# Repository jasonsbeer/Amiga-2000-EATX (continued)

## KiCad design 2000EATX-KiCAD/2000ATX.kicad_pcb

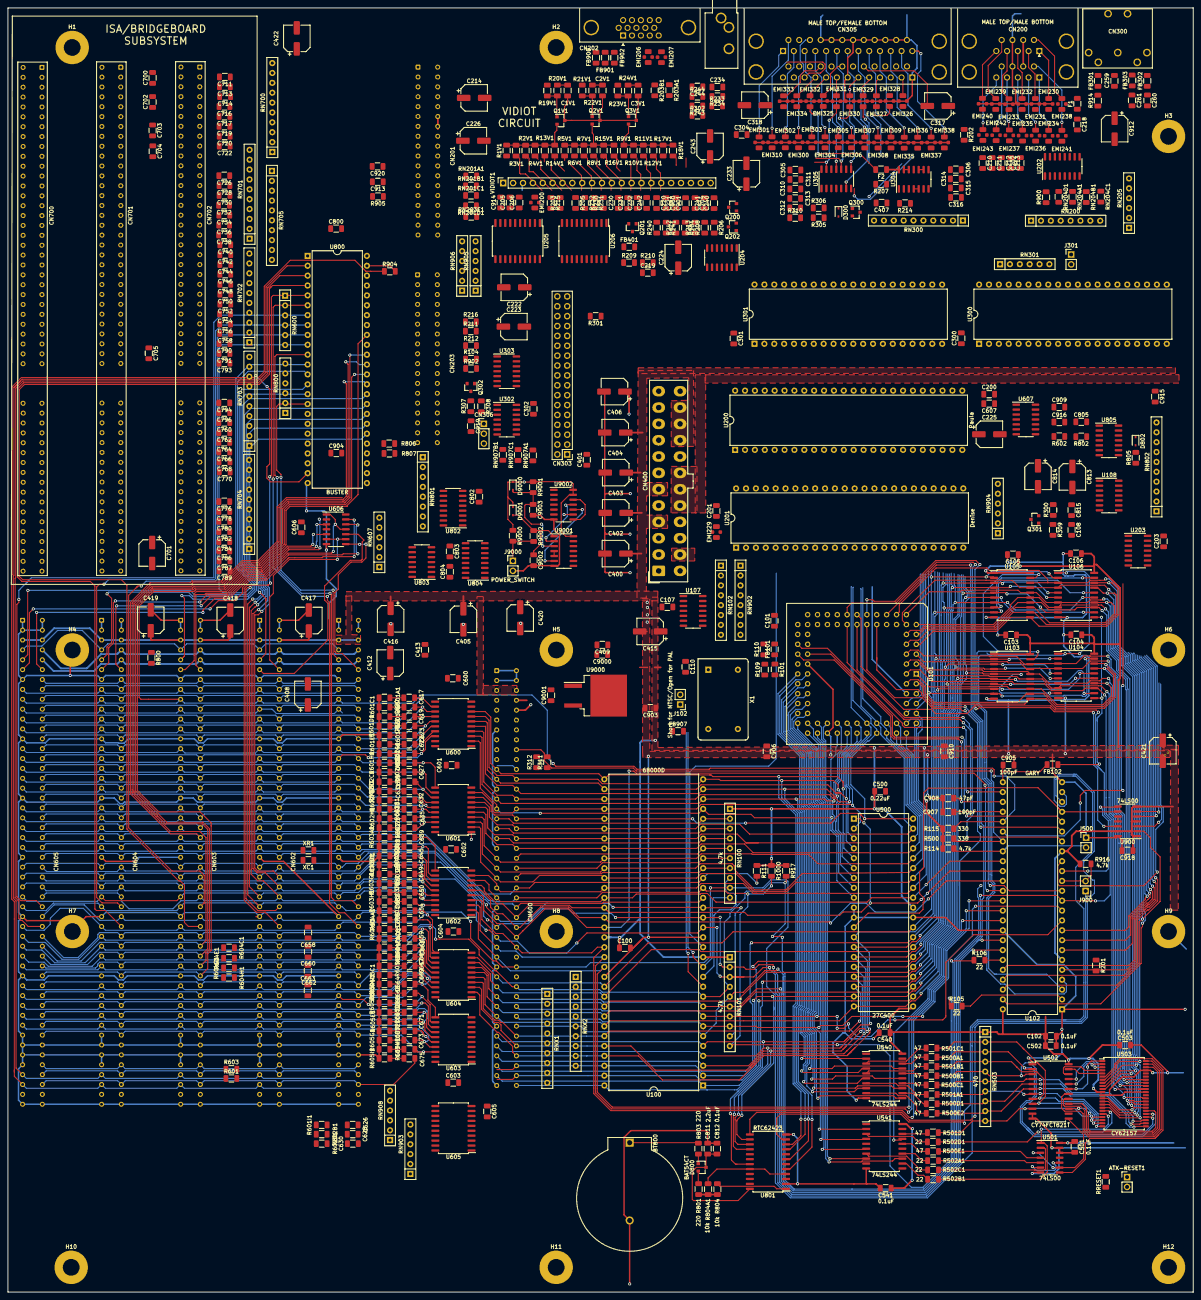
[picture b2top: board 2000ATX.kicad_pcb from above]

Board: 2 copper layers, 304.8 x 330.2 mm, 579 parts (0 on the bottom side), 722 nets.

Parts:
ATX-RESET1: ATX RESET; PinHeader_1x02_P2.54mm_Vertical
BT800: Battery_Cell; BatteryHolder_ComfortableElectronic_CH273-2450_1x2450
C1V1, C2V1, C3V1: 100nF; C_1206_3216Metric
C100, C101, C102, C103, C104, C105, C106, C107, C108, C110, C200, C202, C203, C204, C205, C206, C218, C230, C234, C240, C244, C300, C301, C302, C305, C501, C502, C503, C540, C541, C600, C601, C602, C603, C604, C605, C606, C607, C800, C802, C803, C804, C805, C812, C815, C900, C901, C909, C915, C916, C918, C919: 0.1uF; C_1206_3216Metric
C201, C219, C220, C221, C500, C700, C702, C703, C704, C705: 0.22uF; C_1206_3216Metric
C210, C211, C212, C213: 0.047uF; C_1206_3216Metric
C214, C225, C226, C912: 470uF; CP_Elec_6.3x5.8
C222, C223, C402, C403, C404, C405, C406, C408, C412, C420, C421, C422: 47uF; CP_Elec_6.3x5.8
C224, C415: 4.7uF; CP_Elec_6.3x5.8
C231, C241: 6800pF; C_1206_3216Metric
C232, C242: 3900pF; C_1206_3216Metric
C233, C243, C317, C318, C701, C813, C814: 22uF; CP_Elec_6.3x5.8
C259, C260, C261, C304, C306, C904, C905, C907, C914, C920: 100pF; C_1206_3216Metric
C310, C311, C312, C313, C314, C315, C316, C617, C619, C620, C621, C622, C623, C624, C625, C626, C627, C628, C629, C630, C631, C632, C633, C635, C637, C639, C641, C645, C647, C649, C650, C651, C652, C654, C655, C657, C658, C659, C660, C661, C662, C663, C664, C665, C666, C667, C668, C669, C670, C671, C672, C673, C674, C675, C711, C713, C714, C716, C717, C719, C720, C722, C726, C728, C730, C732, C734, C736, C738, C740, C742, C744, C746, C748, C750, C752, C754, C756, C758, C760, C762, C764, C766, C768, C770, C776, C778, C780, C782, C784, C786, C787, C789, C790, C791, C793, C794, C796: 1000pF; C_1206_3216Metric
C400, C416, C417, C418, C419: 220uF; CP_Elec_6.3x5.8
C401, C407, C409, C413, C903, C906, C910: 0.1uf; C_1206_3216Metric
C811: 2.2uF; C_1206_3216Metric
C908, C913: 47pF; C_1206_3216Metric
C9000, C9002: 1uF; C_1206_3216Metric
C9001: 0.33uF; C_1206_3216Metric
C9003: 10uF; C_1206_3216Metric
CN200: DB9_Male_Stack; DSUB-9_Male_Stack
CN201, CN203: Amiga-2000-Video-Slot; 2x18_P2.54mm_Horizontal
CN202: DB15_Female_HighDensity; DSUB-15-HD_Female_Horizontal_P2.29x1.98mm_EdgePinOffset3.03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
CN205: AudioJack; Jack_3.5mm_CUI_SJ1-3533NG_Horizontal_CircularHoles
CN300: KEYBOARD; DIN5
CN303: FLOPPY; PinHeader_2x17_P2.54mm_Vertical
CN305: DB25_Stack_FemaleAndMale; DSUB-25_Stack_Female_Bottom_Male_Top
CN306: POWER LED; PinHeader_1x03_P2.54mm_Vertical
CN400: ATX-24; Molex_Mini-Fit_Jr_5566-24A_2x12_P4.20mm_Vertical
CN600: Amiga-2000-CPU-Slot; Samtec_HLE-150-02-xx-DV-TE_2x43_P2.54mm_Horizontal
CN601, CN602, CN603, CN604, CN605: Amiga-2000-Zorro-Slot; Samtec_HLE-150-02-xx-DV-TE_2x50_P2.54mm_Horizontal
CN700, CN701, CN702: ISA-16-BIT-Slot; ISA_16-BIT_P2.54mm_Horizontal
D300, D802, D9000, D9001: 1N4148; D_SOD-323
D800: BAT54CT; SOT-23
EMI200, EMI206, EMI207, EMI229, EMI230, EMI231, EMI232, EMI233, EMI234, EMI235, EMI236, EMI237, EMI238, EMI239, EMI240, EMI241, EMI242, EMI243, EMI325, EMI326, EMI327, EMI328, EMI329, EMI330, EMI331, EMI332, EMI333, EMI334: 100pF; C_1206_3216_Feedthrough
EMI300, EMI301, EMI302, EMI303, EMI304, EMI305, EMI306, EMI307, EMI308, EMI309, EMI310, EMI335, EMI336, EMI337, EMI338: C_Feedthrough; C_1206_3216_Feedthrough
F1, F2: 4A; Fuse_1206_3216Metric
FB101, FB102, FB301, FB302, FB303, FB401, FB900, FB901, FB902, FB907: Ferrite_Bead; C_1206_3216Metric
H1, H2, H3, H4, H5, H6, H7, H8, H9, H10, H11, H12: MountingHole_Pad; MountingHole_4.3mm_M4_Pad
J102: Short for NTSC/Open for PAL; PinHeader_1x02_P2.54mm_Vertical
J301: CLOSE FOR DF1; PinHeader_1x02_P2.54mm_Vertical
J500: Conn_01x02_Male; PinHeader_1x02_P2.54mm_Vertical
J900: Enable Chip RAM slowdown during DMA; PinHeader_1x02_P2.54mm_Vertical
J9000: POWER_SWITCH; PinHeader_1x02_P2.54mm_Vertical
Q1V1, Q2V1, Q3V1, Q300: MMBT3904; SOT-23
Q200, Q201: MMBFJ211; SOT-23
Q202, Q301, Q302: MMBT3906; SOT-23
R1V1, R5V1, R9V1, R233, R243, R301, R302, R311, R312, R601, R601A1, R601B1, R601C1, R601D1, R601E1, R601F1, R601G1, R601H1, R601I1, R602, R602A1, R602B1, R602C1, R602D1, R602E1, R602F1, R602G1, R602H1, R602I1, R603, R603A1, R603B1, R603C1, R603D1, R603E1, R603F1, R603G1, R603H1, R603I1, R604, R604A1, R604B1, R604C1, R604D1, R604E1, R604F1, R604G1, R604H1, R604I1, R605, R605A1, R605B1, R605C1, R605D1, R605E1, R605F1, R605G1, R605H1, R605I1, R800, R802, R805, R900: 1k; R_1206_3216Metric
R2V1, R7V1, R11V1: 4k; R_1206_3216Metric
R3V1, R6V1, R10V1: 2k; R_1206_3216Metric
R4V1, R8V1, R12V1: 8k; R_1206_3216Metric
R13V1, R15V1, R17V1, R9002: 470; R_1206_3216Metric
R14V1, R16V1, R18V1, R234, R244: 390; R_1206_3216Metric
R19V1, R20V1, R21V1, R22V1, R23V1, R24V1: 75; R_1206_3216Metric
R101, R109, R201, R300, R309, R500, R806, R807, R902, R916: 4.7k; R_1206_3216Metric
R104: 4.7k; C_1206_3216Metric
R105, R106, R212, R502A1, R502B1, R502C1, R502D1: 22; R_1206_3216Metric
R110, R114, R115: 330; R_1206_3216Metric
R111, R917, R1000: 407; C_1206_3216Metric
R202, R203, R206, R211, R214, R216, R231, R232, R241, R242, R305, R306, R804, R804A1, R9000, R9001: 10k; R_1206_3216Metric
R203A1, R203B1, R500A1, R500B1, R500C1, R500D1, R500E1, R500E2, R501A1, R501B1, R501C1, R501D1, R904, R905: 47; R_1206_3216Metric
R204, R205: 470k; R_1206_3216Metric
R207, R208: 10; R_1206_3216Metric
R209, R210: 1.2k; R_1206_3216Metric
R213: 2.7k; R_1206_3216Metric
R215: 1; R_1206_3216Metric
R230, R240: 360; R_1206_3216Metric
R307: 68; R_1206_3216Metric
R308: 200; R_1206_3216Metric
R310: 47 0.5W; R_1206_3216Metric
R801, R803: 220; R_1206_3216Metric
R914: 1 0.5W; R_1206_3216Metric
RN100, RN101: 4.7k; R_Array_SIP10
RN102, RN902: 47; R_Array_SIP8
RN200, RN801: 4.7k; R_Array_SIP8
RN201A1, RN201B1, RN201C1, RN201D1, RN203E1, RN907A1, RN907B1, RN907C1: 47; R_1206_3216Metric
RN204A1, RN204B1, RN204C1, RN204D1: 68; R_1206_3216Metric
RN205, RN301, RN607, RN800, RN903, RN908: 1k; R_Array_SIP6
RN300: 10k; R_Array_SIP10
RN503: 470; R_Array_SIP10
RN600: 10k; R_Array_SIP6
RN700, RN701, RN702, RN703, RN704, RN705, RN802: 1k; R_Array_SIP10
RN904, RN905, RN906: 4.7k; R_Array_SIP6
RNX1, RNX2: 2.7k; R_Array_SIP10
RRESET1: 1k; R_1206_3216Metric
U100: 68000D; DIP-64_W25.4mm
U101: FATTERAGNUS; PLCC-84_THT-Socket
U102: GARY; DIP-48_W15.24mm
U103, U105, U600, U601, U602, U603, U604, U605: 74LS245; SOIC-20W_7.5x12.8mm_P1.27mm
U104, U106: 74LS373; SOIC-20W_7.5x12.8mm_P1.27mm
U107: 74LS04; SOIC-14_3.9x8.7mm_P1.27mm
U108: 74LS74; SOIC-14_3.9x8.7mm_P1.27mm
U200: Paula; DIP-48_W15.24mm
U201: Denise; DIP-48_W15.24mm
U202: 74LS157; SOIC-16_3.9x9.9mm_P1.27mm
U203: 74LS38; SOIC-14_3.9x8.7mm_P1.27mm
U204: LF347; SOIC-14_3.9x8.7mm_P1.27mm
U205, U206: 74HCT244; SOIC-20W_7.5x12.8mm_P1.27mm
U300: 8520; DIP-40_W15.24mm
U301: U8520; DIP-40_W15.24mm
U302, U606: 74LS32; SOIC-14_3.9x8.7mm_P1.27mm
U303, U607, U803: 74LS08; SOIC-14_3.9x8.7mm_P1.27mm
U304: SN75188DR; SOIC-14_3.9x8.7mm_P1.27mm
U305: SN75189DR; SOIC-14_3.9x8.7mm_P1.27mm
U500: 27C400; DIP-40_W15.24mm
U501, U900: 74LS00; SOIC-14_3.9x8.7mm_P1.27mm
U502: CY74FCT821T; SOIC-24W_7.5x15.4mm_P1.27mm
U503: CY62157; TSOP-II-44_10.16x18.41mm_P0.8mm
U540, U541: 74LS244; SOIC-20W_7.5x12.8mm_P1.27mm
U800: BUSTER; DIP-48_W15.24mm
U801: RTC62423; SOIC-24W_7.5x15.4mm_P1.27mm
U802: 74LS138; SOIC-16_3.9x9.9mm_P1.27mm
U804: 74LS148; SOIC-16_3.9x9.9mm_P1.27mm
U805: LM339; SOIC-14_3.9x8.7mm_P1.27mm
U9000: MC7905; TO-263-2
U9001: 74HC14; SOIC-14_3.9x8.7mm_P1.27mm
U9002: 74HC74; SOIC-14_3.9x8.7mm_P1.27mm
VIDIOT1: HY200; PinSocket_1x22_P2.54mm_Vertical
X1: 28.63636MHz; Oscillator_DIP-14
XC1: 270pf; C_1206_3216Metric
XR1: 68; C_1206_3216Metric

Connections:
7M: RN907A1.1, U100.15, U201.35
28M: CN600.9, FB101.2, U101.34
+3V3: CN400.1, CN400.2, CN400.12, CN400.13
+5V: C100.1, C101.1, C102.1, C103.1, C104.1, C105.1, C106.1, C107.1, C108.2, C110.1, C200.1, C202.2, C203.2, C218.1, C225.1, C300.2, C301.1, C302.2, C305.1, C400.1, C401.1, C402.1, C403.1, C404.1, C405.1, C415.1, C416.1, C417.1, C418.1, C419.1, C420.1, C421.1, C422.1, C500.1, C501.1, C502.1, C503.1, C540.1, C541.1, C605.2, C606.1, C607.2, C700.1, C701.1, C705.1, C800.1, C802.1, C803.1, C804.1, C805.1, C903.1, C906.1, C910.1, C918.1, CN201.6, CN201.8, CN400.4, CN400.6, CN400.21, CN400.22, CN400.23, CN600.5, CN600.6, CN601.5, CN601.6, CN602.5, CN602.6, CN603.5, CN603.6, CN604.5, CN604.6, CN605.5, CN605.6, CN700.B3, CN700.B29, CN700.D16, CN701.B3, CN701.B29, CN701.D16, CN702.B3, CN702.B29, CN702.D16, D802.1, EMI200.1, EMI229.1, F1.1, Q302.1, R101.2, R104.1, R109.2, R111.1, R114.2, R115.2, R201.1, R203.2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
+12V: C406.1, C407.1, C704.1, CN201.10, CN400.10, CN400.11, CN600.10, CN601.10, CN602.10, CN603.10, CN604.10, CN605.10, CN700.B9, CN701.B9, CN702.B9, F2.1, R207.1, U304.14
+AV: C220.1, C222.1, C900.1, Q202.1, R207.2, R213.1, U204.4
+VID: C205.2, C206.2, C214.1, C226.1, R215.1, U205.20, U206.20, VIDIOT1.2, VIDIOT1.21
-5V: C412.1, C413.1, C702.1, C9001.1, CN201.31, CN600.8, CN601.8, CN602.8, CN603.8, CN604.8, CN605.8, CN700.B5, CN701.B5, CN702.B5, U9000.3
-12V: C408.1, C409.1, C703.1, C9000.1, CN400.14, CN601.20, CN602.20, CN603.20, CN604.20, CN605.20, CN700.B7, CN701.B7, CN702.B7, EMI334.2, R208.2, U304.1, U9000.2
-AV: C221.2, C223.2, C901.2, R206.2, R208.1, U204.11
/Floppy and Parallel/CHNG: CN303.2, RN301.2, U300.4
/Floppy and Parallel/DKWDB: CN303.22, U203.8
/Floppy and Parallel/DKWEB: CN303.24, U203.11
/Floppy and Parallel/INUSE1: CN303.4, CN303.14, U108.9, U203.4
/Floppy and Parallel/KBCLK: C260.1, CN300.3, FB302.1
/Floppy and Parallel/KBDATA: C261.1, CN300.2, FB303.1
/Floppy and Parallel/MTROD: CN303.16, Q301.3
/Floppy and Parallel/POUT: CN305.12, EMI337.2
/Floppy and Parallel/RDY: CN303.34, J301.2, RN301.5, U300.7
/Floppy and Parallel/SEL: CN305.13, EMI338.2
/Floppy and Parallel/TRK0: CN303.26, RN301.3, U300.6
/Floppy and Parallel/WPROT: CN303.28, RN301.4, U300.5
/Floppy and Parallel/_INUSE0: CN303.6, U900.3
/Floppy and Parallel/_IORST: C916.1, EMI300.2, U607.8
/Memory and Kickstart/DRAB0: R500A1.1, RN503.3, U502.2, U503.27
/Memory and Kickstart/DRAB1: R500B1.1, RN503.5, U502.3, U503.26
/Memory and Kickstart/DRAB2: R500C1.1, RN503.6, U502.4, U503.25
/Memory and Kickstart/DRAB3: R500D1.1, RN503.8, U502.5, U503.24
/Memory and Kickstart/DRAB4: R500E2.1, RN503.9, U502.6, U503.23
/Memory and Kickstart/DRAB5: R501A1.1, RN503.7, U502.7, U503.22
/Memory and Kickstart/DRAB6: R501B1.1, RN503.4, U502.8, U503.21
/Memory and Kickstart/DRAB7: R501C1.1, RN503.2, U502.9, U503.20
/Memory and Kickstart/DRAB8: R501D1.1, RN503.10, U502.10, U503.19
/Memory and Kickstart/DRAC0: U502.23, U503.5
/Memory and Kickstart/DRAC1: U502.22, U503.4
/Memory and Kickstart/DRAC2: U502.21, U503.3
/Memory and Kickstart/DRAC3: U502.20, U503.2
/Memory and Kickstart/DRAC4: U502.19, U503.1
/Memory and Kickstart/DRAC5: U502.18, U503.44
/Memory and Kickstart/DRAC6: U502.17, U503.43
/Memory and Kickstart/DRAC7: U502.16, U503.42
/Memory and Kickstart/DRAC8: U502.15, U503.28
/Memory and Kickstart/_CAS: U501.6, U501.10
/Memory and Kickstart/_MCASL: R500E1.1, U501.4
/Memory and Kickstart/_MCASU: R502A1.1, U501.5
/Memory and Kickstart/_MEMCLK: U501.3, U501.9, U502.13
/Memory and Kickstart/_MRAS0: R502B1.1, U501.1, U503.18
/Memory and Kickstart/_MRAS1: R502C1.1, U501.2
/Memory and Kickstart/_MWE: R502D1.1, U503.17
/Memory and Kickstart/_SRAMCE: U501.8, U503.6
/Paula/+5VMOUSE: CN200.7, CN200.16, F1.2
/Paula/FIR0: CN200.15, EMI241.1
/Power/+5VSB: CN400.9, D9000.1, D9001.1, R9000.1, R9001.1, U9001.14, U9002.13, U9002.14
/Power/PS_ON: CN400.16, U9002.9
/Serial/+V: CN305.34, EMI332.1
/Serial/-V: CN305.35, EMI334.1
/Serial/AI: C306.1, C317.2, CN305.43
/Serial/AO: C304.1, C318.1, CN305.36
/Serial/CD: CN305.33, EMI331.2, U301.7, U305.11
/Serial/CTS: CN305.30, EMI329.2, U301.6, U305.6
/Serial/DSR: CN305.31, EMI330.2, U301.5, U305.8
/Serial/DTR: CN305.45, EMI325.2, U301.9, U304.12, U304.13
/Serial/RI: CN305.47, EMI333.1
/Serial/RTS: CN305.29, EMI327.2, U301.8, U304.4, U304.5
/Serial/RxD: CN305.28, EMI328.2
/Serial/TxD: CN305.27, EMI326.2
/Video/BLUE: C3V1.2, CN201.15, FB902.2, R18V1.1, R24V1.2, VIDIOT1.17
/Video/BURST: CN201.18, U205.16
/Video/COMPSYNC: CN201.28, VIDIOT1.20
/Video/DB_(B3): CN201.25, RN201B1.2
/Video/DG_(G3): CN201.27, RN201C1.2
/Video/DI_(B0): CN201.23, RN201A1.2
/Video/DR_(R3): CN201.29, RN201D1.2
/Video/GREEN: C2V1.2, CN201.11, FB901.2, R16V1.1, R22V1.2, VIDIOT1.12
/Video/HSYNC: EMI206.1, R203B1.1
/Video/PIXELSW: CN201.30, RN203E1.1
/Video/RED: C1V1.2, CN201.7, FB900.2, R14V1.1, R20V1.2, VIDIOT1.7
/Video/VSYNC: EMI207.1, R203A1.1
/Zorro_Expansion/_CFGIN1: CN605.11, RN607.5, U606.13
/Zorro_Expansion/_CFGIN2: CN604.11, RN607.4, U606.2
/Zorro_Expansion/_CFGIN3: CN603.11, RN607.3, U606.5
/Zorro_Expansion/_CFGIN4: CN602.11, RN607.2, U606.10
/Zorro_Expansion/_CFGOUT2: CN604.12, U606.1, U606.11
/Zorro_Expansion/_CFGOUT3: CN603.12, U606.3, U606.4
/Zorro_Expansion/_CFGOUT4: CN602.12, U606.6, U606.9
/Zorro_Expansion/_CFGOUT5: CN601.12, U606.8
A1: CN600.29, U100.29, U101.60, U500.9, U600.2
A2: CN600.27, U100.30, U101.61, U500.8, U600.3, U801.5
A3: CN600.26, U100.31, U101.62, U500.7, U600.5, U801.7
A4: CN600.24, U100.32, U101.63, U500.6, U600.7, U801.9
A5: CN600.21, U100.33, U101.64, U500.5, U600.8, U801.10
A6: CN600.23, U100.34, U101.65, U500.4, U600.6
A7: CN600.28, U100.35, U101.66, U500.3, U600.4
A8: CN600.30, U100.36, U101.67, U300.38, U301.38, U500.2, U601.9
A9: CN600.32, U100.37, U101.68, U300.37, U301.37, U500.40, U601.8
A10: CN600.34, U100.38, U101.69, U300.36, U301.36, U500.39, U601.7
A11: CN600.36, U100.39, U101.70, U300.35, U301.35, U500.38, U601.6
A12: CN600.38, U100.40, U101.71, U302.1, U500.37, U601.5
A13: CN600.39, U100.41, U101.72, U302.5, U500.36, U601.4
A14: CN600.41, U100.42, U101.73, U500.35, U601.3
A15: CN600.43, U100.43, U101.74, U500.34, U601.2
A16: CN600.45, U100.44, U101.75, U500.33, U602.9
A17: CN600.47, U100.45, U101.76, U102.33, U500.32, U602.8
A18: CN600.52, U100.46, U101.77, U102.34, U500.1, U602.7
A19: CN600.54, U100.47, U101.59, U102.35, U602.6
A20: CN600.56, U100.48, U102.36, U602.5
A21: CN600.58, U100.50, U102.37, U602.4
A22: CN600.57, U100.51, U102.38, U602.3
A23: CN600.59, U100.52, U102.39, U602.2
AUDIN: C317.1, R202.1
AUDIO: C204.2, C219.2, C220.2, C221.1, C222.2, C223.1, C224.2, C232.2, C242.2, C900.2, C901.1, CN203.34, CN203.36, FB401.2, R210.2
AUDOUT: C243.2, R243.2, R302.1
B0: R12V1.2, RN201A1.1, U206.9, VIDIOT1.16
B1: CN203.10, R11V1.2, U206.7, VIDIOT1.15
B2: CN203.11, R10V1.2, U206.5, VIDIOT1.14
B3: R9V1.2, RN201B1.1, U206.3, VIDIOT1.13
BA1: C624.2, CN601.29, CN602.29, CN603.29, CN604.29, CN605.29, U600.18
BA2: C622.2, CN601.27, CN602.27, CN603.27, CN604.27, CN605.27, U600.17
BA3: C621.2, CN601.26, CN602.26, CN603.26, CN604.26, CN605.26, U600.15
BA4: C620.2, CN601.24, CN602.24, CN603.24, CN604.24, CN605.24, U600.13
BA5: C617.2, CN601.21, CN602.21, CN603.21, CN604.21, CN605.21, U600.12
BA6: C619.2, CN601.23, CN602.23, CN603.23, CN604.23, CN605.23, U600.14
BA7: C623.2, CN601.28, CN602.28, CN603.28, CN604.28, CN605.28, U600.16
BA8: C625.2, CN601.30, CN602.30, CN603.30, CN604.30, CN605.30, U601.11
BA9: C627.2, CN601.32, CN602.32, CN603.32, CN604.32, CN605.32, U601.12
BA10: C629.2, CN601.34, CN602.34, CN603.34, CN604.34, CN605.34, U601.13
BA11: C631.2, CN601.36, CN602.36, CN603.36, CN604.36, CN605.36, U601.14
BA12: C632.2, CN601.38, CN602.38, CN603.38, CN604.38, CN605.38, U601.15
BA13: C633.2, CN601.39, CN602.39, CN603.39, CN604.39, CN605.39, U601.16
BA14: C635.2, CN601.41, CN602.41, CN603.41, CN604.41, CN605.41, U601.17
BA15: C637.2, CN601.43, CN602.43, CN603.43, CN604.43, CN605.43, U601.18
BA16: C639.2, CN601.45, CN602.45, CN603.45, CN604.45, CN605.45, U602.11
BA17: C641.2, CN601.47, CN602.47, CN603.47, CN604.47, CN605.47, U602.12
BA18: C645.2, CN601.52, CN602.52, CN603.52, CN604.52, CN605.52, U602.13
BA19: C647.2, CN601.54, CN602.54, CN603.54, CN604.54, CN605.54, U602.14, U800.30
BA20: C649.2, CN601.56, CN602.56, CN603.56, CN604.56, CN605.56, U602.15, U800.31
BA21: C651.2, CN601.58, CN602.58, CN603.58, CN604.58, CN605.58, U602.16, U800.32
BA22: C650.2, CN601.57, CN602.57, CN603.57, CN604.57, CN605.57, U602.17, U800.33
BA23: C652.2, CN601.59, CN602.59, CN603.59, CN604.59, CN605.59, U602.18, U800.34
BD0: C664.2, CN601.75, CN602.75, CN603.75, CN604.75, CN605.75, U603.11
BD1: C666.2, CN601.77, CN602.77, CN603.77, CN604.77, CN605.77, U603.12
BD2: C668.2, CN601.79, CN602.79, CN603.79, CN604.79, CN605.79, U603.13
BD3: C670.2, CN601.81, CN602.81, CN603.81, CN604.81, CN605.81, U603.14
BD4: C672.2, CN601.83, CN602.83, CN603.83, CN604.83, CN605.83, U603.16
BD5: C674.2, CN601.86, CN602.86, CN603.86, CN604.86, CN605.86, U603.18
BD6: C673.2, CN601.84, CN602.84, CN603.84, CN604.84, CN605.84, U603.17
BD7: C671.2, CN601.82, CN602.82, CN603.82, CN604.82, CN605.82, U603.15
BD8: C669.2, CN601.80, CN602.80, CN603.80, CN604.80, CN605.80, U604.18
BD9: C667.2, CN601.78, CN602.78, CN603.78, CN604.78, CN605.78, U604.17
BD10: C665.2, CN601.76, CN602.76, CN603.76, CN604.76, CN605.76, U604.16
BD11: C661.2, CN601.71, CN602.71, CN603.71, CN604.71, CN605.71, U604.15
BD12: C659.2, CN601.69, CN602.69, CN603.69, CN604.69, CN605.69, U604.14
BD13: C657.2, CN601.67, CN602.67, CN603.67, CN604.67, CN605.67, U604.13
BD14: C655.2, CN601.65, CN602.65, CN603.65, CN604.65, CN605.65, U604.12
BD15: C654.2, CN601.63, CN602.63, CN603.63, CN604.63, CN605.63, U604.11
BFC0: C626.2, CN601.31, CN602.31, CN603.31, CN604.31, CN605.31, RN903.6, U605.15
BFC1: C628.2, CN601.33, CN602.33, CN603.33, CN604.33, CN605.33, RN903.5, U605.16
BFC2: C630.2, CN601.35, CN602.35, CN603.35, CN604.35, CN605.35, RN903.4, U605.17
C1: C907.1, U101.40, U102.28, U107.3, U107.13, U200.28, U201.36, U800.19
C3: C908.1, U101.39, U102.27, U107.5, U107.9, U200.29, U800.20
D0: CN305.2, CN600.75, EMI302.2, RNX1.3, U100.5, U105.2, U106.2, U300.33, U301.33, U500.13, U603.9, U801.19
D1: CN305.3, CN600.77, EMI303.2, RNX1.4, U100.4, U105.3, U106.5, U300.32, U301.32, U500.15, U603.8, U801.16
D2: CN305.4, CN600.79, EMI304.2, RNX1.5, U100.3, U105.4, U106.6, U300.31, U301.31, U500.17, U603.7, U801.15
D3: CN305.5, CN600.81, EMI305.2, RNX1.6, U100.2, U105.5, U106.9, U300.30, U301.30, U500.19, U603.6, U801.14
D4: CN305.6, CN600.83, EMI306.2, RNX1.10, U100.1, U105.6, U106.12, U300.29, U301.29, U500.22, U603.4
D5: CN305.7, CN600.86, EMI307.2, RNX1.9, U100.64, U105.7, U106.15, U300.28, U301.28, U500.24, U603.2
D6: CN305.8, CN600.84, EMI308.2, RNX1.8, U100.63, U105.8, U106.16, U300.27, U301.27, U500.26, U603.3
D7: CN305.9, CN600.82, EMI309.2, RNX1.7, U100.62, U105.9, U106.19, U300.26, U301.26, U500.28, U603.5
D8: CN600.80, RNX2.9, U100.61, U103.2, U104.2, U500.14, U604.2
D9: CN600.78, RNX2.8, U100.60, U103.3, U104.5, U500.16, U604.3
D10: CN600.76, RNX2.7, U100.59, U103.4, U104.6, U500.18, U604.4
D11: CN600.71, RNX2.6, U100.58, U103.5, U104.9, U500.20, U604.5
D12: CN600.69, RNX2.5, U100.57, U103.6, U104.12, U500.23, U604.6
D13: CN600.67, RNX2.4, U100.56, U103.7, U104.15, U500.25, U604.7
D14: CN600.65, RNX2.3, U100.55, U103.8, U104.16, U500.27, U604.8
D15: CN600.63, RNX2.2, U100.54, U103.9, U104.19, U500.29, U604.9
DIR: CN303.18, U301.11
DKWE: U102.8, U200.39
DMAL: U101.18, U200.12
DMAOUT: U302.11, U600.1, U601.1, U602.1, U605.1
DOE: CN601.93, CN602.93, CN603.93, CN604.93, CN605.93, R601.2, R904.1
DRA0: U101.43, U540.2
DRA1: U101.44, U540.4
DRA2: U101.45, U540.6
DRA3: U101.46, U540.8
DRA4: U101.47, U540.17
DRA5: U101.48, U540.15
DRA6: U101.49, U540.13
DRA7: U101.50, U540.11
DRA8: U101.51, U541.2
DRD0: U101.14, U105.18, U106.3, U200.10, U201.7, U503.7
DRD1: U101.13, U105.17, U106.4, U200.9, U201.6, U503.8
DRD2: U101.12, U105.16, U106.7, U200.7, U201.5, U503.9
DRD3: U101.11, U105.15, U106.8, U200.6, U201.4, U503.10
DRD4: U101.10, U105.14, U106.13, U200.5, U201.3, U503.13
DRD5: U101.9, U105.13, U106.14, U200.4, U201.2, U503.14
DRD6: U101.8, U105.12, U106.17, U200.3, U201.1, U503.15
DRD7: U101.7, U105.11, U106.18, U200.2, U201.48, U503.16
DRD8: U101.6, U103.18, U104.3, U200.1, U201.47, U503.29
DRD9: U101.5, U103.17, U104.4, U200.48, U201.46, U503.30
DRD10: U101.4, U103.16, U104.7, U200.47, U201.45, U503.31
DRD11: U101.3, U103.15, U104.8, U200.46, U201.44, U503.32
DRD12: U101.2, U103.14, U104.13, U200.45, U201.43, U503.35
DRD13: U101.1, U103.13, U104.14, U200.44, U201.42, U503.36
DRD14: U101.84, U103.12, U104.17, U200.43, U201.41, U503.37
DRD15: U101.83, U103.11, U104.18, U200.42, U201.40, U503.38
E: CN600.50, CN601.50, CN602.50, CN603.50, CN604.50, CN605.50, U100.20, U300.25, U301.25, XR1.1
E7M: CN601.92, CN602.92, CN603.92, CN604.92, CN605.92, RN907B1.1
ECDAC: CN601.15, CN602.15, CN603.15, CN604.15, CN605.15, RN902.8
FC0: CN600.31, RN100.2, U100.28, U605.5
FC1: CN600.33, RN100.3, U100.27, U605.4
FC2: CN600.35, RN100.4, U100.26, U605.3
FLTLEFT: C244.1, CN201.3, CN205.T, R243.1, R244.2
FLTRIGHT: C234.1, CN201.4, CN205.R, R233.1, R234.2
G0: CN203.6, R8V1.2, U206.12, VIDIOT1.11
G1: CN203.7, R7V1.2, U206.14, VIDIOT1.10
G2: CN203.8, R6V1.2, U206.16, VIDIOT1.9
G3: R5V1.2, RN201C1.1, U206.18, VIDIOT1.8
GND: BT800.2, C100.2, C101.2, C102.2, C103.2, C104.2, C105.2, C106.2, C107.2, C108.1, C110.2, C200.2, C201.2, C202.1, C203.1, C205.1, C206.1, C210.2, C211.2, C212.2, C213.2, C214.2, C218.2, C225.2, C226.2, C234.2, C244.2, C259.2, C260.2, C261.2, C300.1, C301.2, C302.1, C304.2, C305.2, C306.2, C310.2, C311.2, C312.2, C313.2, C314.1, C315.1, C316.1, C400.2, C401.2, C402.2, C403.2, C404.2, C405.2, C406.2, C407.2, C408.2, C409.2, C412.2, C413.2, C415.2, C416.2, C417.2, C418.2, C419.2, C420.2, C421.2, C422.2, C500.2, C501.2, C502.2, C503.2, C540.2, C541.2, C600.2, C601.2, C602.2, C603.2, C604.2, C605.1, C606.2, C607.1, C700.2, C701.2, C702.2, C703.2, C704.2, C705.2, C800.2, C802.2, C803.2, C804.2, C805.2, C811.2, C812.2, C814.2, C815.2, C903.2, C904.2, C905.2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
M0H: RN204D1.2, RN205.6, U201.9
M0V: RN204C1.2, RN205.5, U201.38
M1H: RN204B1.2, RN205.4, U201.8
M1V: RN204A1.2, RN205.3, U201.39
unnamed: ATX-RESET1.2, RRESET1.1
unnamed: BT800.1, R803.1
unnamed: C1V1.1, Q1V1.3, R13V1.2
unnamed: C2V1.1, Q2V1.3, R15V1.2
unnamed: C3V1.1, Q3V1.3, R17V1.2
unnamed: C201.1, EMI229.2, RN904.1, RN905.1, RN906.1, U201.19
unnamed: C204.1, Q202.3, R204.1, R205.1, R206.1
unnamed: C210.1, EMI243.1, U200.32
unnamed: C211.1, EMI242.1, U200.33
unnamed: C212.1, EMI240.2, U200.35
unnamed: C213.1, EMI239.2, U200.36
unnamed: C230.2, R202.2, R230.2, U200.30, U204.9
unnamed: C231.1, C233.1, U204.6, U204.7
unnamed: C231.2, R231.1, R232.2
unnamed: C232.1, Q201.1, R232.1, U204.5
unnamed: C233.2, R233.2
unnamed: C240.2, R240.2, U200.31, U204.13
unnamed: C241.1, U204.2
unnamed: C241.2, R241.1, R242.2
unnamed: C242.1, Q200.1, R242.1, U204.3
unnamed: C243.1, U204.1
unnamed: C259.1, C912.1, CN300.4, FB301.1
unnamed: C310.1, EMI331.1, U305.13
unnamed: C311.1, EMI330.1, U305.10
unnamed: C312.1, EMI329.1, U305.4
unnamed: C313.1, EMI328.1, U305.1
unnamed: C314.2, EMI325.1, U304.11
unnamed: C315.2, EMI326.1, U304.8
unnamed: C316.2, EMI327.1, U304.6
unnamed: C318.2, R302.2
unnamed: C600.1, U600.20
unnamed: C601.1, U601.20
unnamed: C602.1, U602.20
unnamed: C603.1, U603.20
unnamed: C604.1, U604.20
unnamed: C617.1, R601A1.2
unnamed: C619.1, R601B1.2
unnamed: C620.1, R601C1.2
unnamed: C621.1, R601D1.2
unnamed: C622.1, R601E1.2
unnamed: C623.1, R601F1.2
unnamed: C624.1, R601G1.2
unnamed: C625.1, R601H1.2
unnamed: C626.1, R601I1.2
unnamed: C627.1, R602A1.2
unnamed: C628.1, R602B1.2
unnamed: C629.1, R602C1.2
unnamed: C630.1, R602D1.2
unnamed: C631.1, R602E1.2
unnamed: C632.1, R602F1.2
unnamed: C633.1, R602G1.2
unnamed: C635.1, R602H1.2
unnamed: C637.1, R602I1.2
unnamed: C639.1, R603A1.2
unnamed: C641.1, R603B1.2
unnamed: C645.1, R603C1.2
unnamed: C647.1, R603D1.2
unnamed: C649.1, R603E1.2
unnamed: C650.1, R603F1.2
unnamed: C651.1, R603G1.2
unnamed: C652.1, R603H1.2
unnamed: C654.1, R603I1.2
unnamed: C655.1, R604A1.2
unnamed: C657.1, R604B1.2
unnamed: C658.1, R604C1.2
unnamed: C659.1, R604D1.2
unnamed: C660.1, R604E1.2
unnamed: C661.1, R604F1.2
unnamed: C662.1, R604G1.2
unnamed: C663.1, R604H1.2
unnamed: C664.1, R604I1.2
unnamed: C665.1, R604.2
unnamed: C666.1, R605.2
unnamed: C667.1, R605A1.2
unnamed: C668.1, R605B1.2
unnamed: C669.1, R605C1.2
unnamed: C670.1, R605D1.2
unnamed: C671.1, R605E1.2
unnamed: C672.1, R605F1.2
unnamed: C673.1, R605G1.2
unnamed: C674.1, R605H1.2
unnamed: C675.1, R605I1.2
unnamed: C711.1, RN700.10
unnamed: C711.2, CN700.A2, CN701.A2, CN702.A2
unnamed: C713.1, RN700.9
unnamed: C713.2, CN700.A3, CN701.A3, CN702.A3
unnamed: C714.1, RN700.8
unnamed: C714.2, CN700.A4, CN701.A4, CN702.A4
unnamed: C716.1, RN700.7
unnamed: C716.2, CN700.A5, CN701.A5, CN702.A5
unnamed: C717.1, RN700.6
unnamed: C717.2, CN700.A6, CN701.A6, CN702.A6
unnamed: C719.1, RN700.5
unnamed: C719.2, CN700.A7, CN701.A7, CN702.A7
unnamed: C720.1, RN700.4
unnamed: C720.2, CN700.A8, CN701.A8, CN702.A8
unnamed: C722.1, RN700.3
unnamed: C722.2, CN700.A9, CN701.A9, CN702.A9
unnamed: C726.1, RN700.2
unnamed: C726.2, CN700.A12, CN701.A12, CN702.A12
unnamed: C728.1, RN701.10
unnamed: C728.2, CN700.A13, CN701.A13, CN702.A13
unnamed: C730.1, RN701.9
unnamed: C730.2, CN700.A14, CN701.A14, CN702.A14
unnamed: C732.1, RN701.8
unnamed: C732.2, CN700.A15, CN701.A15, CN702.A15
unnamed: C734.1, RN701.7
unnamed: C734.2, CN700.A16, CN701.A16, CN702.A16
unnamed: C736.1, RN701.6
unnamed: C736.2, CN700.A17, CN701.A17, CN702.A17
unnamed: C738.1, RN701.5
unnamed: C738.2, CN700.A18, CN701.A18, CN702.A18
unnamed: C740.1, RN701.4
unnamed: C740.2, CN700.A19, CN701.A19, CN702.A19
unnamed: C742.1, RN701.3
unnamed: C742.2, CN700.A20, CN701.A20, CN702.A20
unnamed: C744.1, RN701.2
unnamed: C744.2, CN700.A21, CN701.A21, CN702.A21
unnamed: C746.1, RN702.10
unnamed: C746.2, CN700.A22, CN701.A22, CN702.A22
unnamed: C748.1, RN702.9
unnamed: C748.2, CN700.A23, CN701.A23, CN702.A23
unnamed: C750.1, RN702.8
unnamed: C750.2, CN700.A24, CN701.A24, CN702.A24
unnamed: C752.1, RN702.7
unnamed: C752.2, CN700.A25, CN701.A25, CN702.A25
unnamed: C754.1, RN702.6
unnamed: C754.2, CN700.A26, CN701.A26, CN702.A26
unnamed: C756.1, RN702.5
unnamed: C756.2, CN700.A27, CN701.A27, CN702.A27
unnamed: C758.1, RN702.4
unnamed: C758.2, CN700.A28, CN701.A28, CN702.A28
unnamed: C760.1, RN703.7
unnamed: C760.2, CN700.C3, CN701.C3, CN702.C3
unnamed: C762.1, RN703.6
unnamed: C762.2, CN700.C4, CN701.C4, CN702.C4
unnamed: C764.1, RN703.5
unnamed: C764.2, CN700.C5, CN701.C5, CN702.C5
unnamed: C766.1, RN703.4
unnamed: C766.2, CN700.C6, CN701.C6, CN702.C6
unnamed: C768.1, RN703.3
unnamed: C768.2, CN700.C7, CN701.C7, CN702.C7
unnamed: C770.1, RN703.2
unnamed: C770.2, CN700.C8, CN701.C8, CN702.C8
unnamed: C776.1, RN704.9
unnamed: C776.2, CN700.C11, CN701.C11, CN702.C11
unnamed: C778.1, RN704.8
unnamed: C778.2, CN700.C12, CN701.C12, CN702.C12
unnamed: C780.1, RN704.7
unnamed: C780.2, CN700.C13, CN701.C13, CN702.C13
unnamed: C782.1, RN704.6
unnamed: C782.2, CN700.C14, CN701.C14, CN702.C14
unnamed: C784.1, RN704.5
unnamed: C784.2, CN700.C15, CN701.C15, CN702.C15
unnamed: C786.1, RN704.4
unnamed: C786.2, CN700.C16, CN701.C16, CN702.C16
unnamed: C787.1, RN704.3
unnamed: C787.2, CN700.C17, CN701.C17, CN702.C17
unnamed: C789.1, RN704.2
unnamed: C789.2, CN700.C18, CN701.C18, CN702.C18
unnamed: C790.1, RN702.3
unnamed: C790.2, CN700.A29, CN701.A29, CN702.A29
unnamed: C791.1, RN702.2
unnamed: C791.2, CN700.A30, CN701.A30, CN702.A30
unnamed: C793.1, RN703.10
unnamed: C793.2, CN700.A31, CN701.A31, CN702.A31
unnamed: C794.1, RN703.9
unnamed: C794.2, CN700.C1, CN701.C1, CN702.C1
unnamed: C796.1, RN703.8
unnamed: C796.2, CN700.C2, CN701.C2, CN702.C2
unnamed: C811.1, C812.1, D800.3, U801.24
unnamed: C813.1, R802.1, U805.1, U805.4
unnamed: C813.2, C815.1, RN802.1, RN802.4, RN802.5, U805.5, U805.7, U805.9
unnamed: C814.1, D802.2, R805.2, U805.2, U805.10
unnamed: C905.1, FB102.2, U102.25
unnamed: C919.1, CN306.2, R307.1, R308.2
unnamed: C9002.1, D9001.2, R9002.1, U9001.1
unnamed: C9002.2, C9003.2, J9000.2, U9001.7, U9002.7
unnamed: C9003.1, D9000.2, R9001.2, U9001.3
unnamed: CN200.1, EMI230.2
unnamed: CN200.2, EMI231.2
unnamed: CN200.3, EMI232.2
unnamed: CN200.4, EMI233.2
unnamed: CN200.5, EMI240.1
unnamed: CN200.6, EMI238.1
unnamed: CN200.9, EMI239.1
unnamed: CN200.10, EMI234.2
unnamed: CN200.11, EMI236.2
unnamed: CN200.12, EMI235.2
unnamed: CN200.13, EMI237.2
unnamed: CN200.14, EMI243.2
unnamed: CN200.18, EMI242.2
unnamed: CN201.33, R211.2, U303.2
unnamed: CN202.1, FB900.1
unnamed: CN202.2, FB901.1
unnamed: CN202.3, FB902.1
unnamed: CN202.13, EMI206.2
unnamed: CN202.14, EMI207.2
unnamed: CN305.1, EMI301.2
unnamed: CN305.10, EMI335.2
unnamed: CN305.11, EMI336.2
unnamed: CN305.14, EMI310.1
unnamed: CN305.16, EMI300.1
unnamed: CN601.97, CN602.97, CN603.97, CN604.97, CN605.97
unnamed: CN601.98, CN602.98, CN603.98, CN604.98, CN605.98
unnamed: CN700.A1, CN701.A1, CN702.A1
unnamed: CN700.A10, CN701.A10, CN702.A10
unnamed: CN700.A11, CN701.A11, CN702.A11
unnamed: CN700.B2, CN701.B2, CN702.B2
unnamed: CN700.B4, CN701.B4, CN702.B4
unnamed: CN700.B6, CN701.B6, CN702.B6
unnamed: CN700.B8, CN701.B8, CN702.B8
unnamed: CN700.B11, CN701.B11, CN702.B11, RN705.2
unnamed: CN700.B12, CN701.B12, CN702.B12, RN705.3
unnamed: CN700.B13, CN701.B13, CN702.B13, RN705.4
unnamed: CN700.B14, CN701.B14, CN702.B14, RN705.5
unnamed: CN700.B15, CN701.B15, CN702.B15
unnamed: CN700.B16, CN701.B16, CN702.B16
unnamed: CN700.B17, CN701.B17, CN702.B17
unnamed: CN700.B18, CN701.B18, CN702.B18
unnamed: CN700.B19, CN701.B19, CN702.B19
unnamed: CN700.B20, CN701.B20, CN702.B20
unnamed: CN700.B21, CN701.B21, CN702.B21
unnamed: CN700.B22, CN701.B22, CN702.B22
unnamed: CN700.B23, CN701.B23, CN702.B23
unnamed: CN700.B24, CN701.B24, CN702.B24
unnamed: CN700.B25, CN701.B25, CN702.B25
unnamed: CN700.B26, CN701.B26, CN702.B26
unnamed: CN700.B27, CN701.B27, CN702.B27
unnamed: CN700.B28, CN701.B28, CN702.B28
unnamed: CN700.B30, CN701.B30, CN702.B30
unnamed: CN700.C9, CN701.C9, CN702.C9, RN705.8
unnamed: CN700.C10, CN701.C10, CN702.C10, RN705.9
unnamed: CN700.D1, CN701.D1, CN702.D1, RN705.6
unnamed: CN700.D2, CN701.D2, CN702.D2, RN705.7
unnamed: CN700.D3, CN701.D3, CN702.D3
unnamed: CN700.D4, CN701.D4, CN702.D4
unnamed: CN700.D5, CN701.D5, CN702.D5
unnamed: CN700.D6, CN701.D6, CN702.D6
unnamed: CN700.D7, CN701.D7, CN702.D7
unnamed: CN700.D8, CN701.D8, CN702.D8
unnamed: CN700.D9, CN701.D9, CN702.D9
unnamed: CN700.D10, CN701.D10, CN702.D10
unnamed: CN700.D11, CN701.D11, CN702.D11
unnamed: CN700.D12, CN701.D12, CN702.D12
unnamed: CN700.D13, CN701.D13, CN702.D13
unnamed: CN700.D14, CN701.D14, CN702.D14
unnamed: CN700.D15, CN701.D15, CN702.D15
unnamed: CN700.D17, CN701.D17, CN702.D17
unnamed: D300.1, Q300.1, R305.1, R306.2
unnamed: D800.1, R803.2
unnamed: D800.2, R801.2
unnamed: EMI200.2, R215.2
unnamed: EMI230.1, RN200.2, U202.2
unnamed: EMI231.1, RN200.4, U202.5
unnamed: EMI232.1, RN200.3, U202.3
unnamed: EMI233.1, RN200.5, U202.6
unnamed: EMI234.1, RN200.6, U202.11
unnamed: EMI235.1, RN200.7, U202.10
unnamed: EMI236.1, RN200.8, U202.14
unnamed: EMI237.1, U202.13
unnamed: EMI310.2, R310.1
unnamed: EMI332.2, F2.2
unnamed: EMI333.2, R306.1
unnamed: FB101.1, X1.8
unnamed: FB301.2, R914.2
unnamed: FB303.2, RN300.10, U300.39
unnamed: FB907.2, RN102.2
unnamed: J102.1, R101.1, U101.41
unnamed: J301.1, U203.6
unnamed: J900.2, R916.1, U102.14
unnamed: J9000.1, R9000.2, R9002.2
unnamed: Q1V1.1, R19V1.2
unnamed: Q1V1.2, R1V1.1, R2V1.1, R3V1.1, R4V1.1, R13V1.1, R14V1.2
unnamed: Q2V1.1, R21V1.2, R22V1.1
unnamed: Q2V1.2, R5V1.1, R6V1.1, R7V1.1, R8V1.1, R15V1.1, R16V1.2
unnamed: Q3V1.1, R23V1.2, R24V1.1
unnamed: Q3V1.2, R9V1.1, R10V1.1, R11V1.1, R12V1.1, R17V1.1, R18V1.2
unnamed: Q200.3, R204.2
unnamed: Q201.3, R205.2
unnamed: Q202.2, R213.2, R214.2
unnamed: Q301.2, R300.1, R309.1
unnamed: Q302.2, R902.1
unnamed: Q302.3, R307.2
unnamed: R105.2, U102.2
unnamed: R106.2, U102.43
unnamed: R212.2, U303.3
unnamed: R216.2, U303.1
unnamed: R300.2, U108.8
unnamed: R309.2, U102.46, U900.2
unnamed: R500A1.2, U540.18
unnamed: R500B1.2, U540.16
unnamed: R500C1.2, U540.14
unnamed: R500D1.2, U540.12
unnamed: R500E1.2, U541.16
unnamed: R500E2.2, U540.9
unnamed: R501A1.2, U540.7
unnamed: R501B1.2, U540.5
unnamed: R501C1.2, U540.3
unnamed: R501D1.2, U541.18
unnamed: R502A1.2, U541.14
unnamed: R502B1.2, U541.12
unnamed: R502C1.2, U541.7
unnamed: R502D1.2, U541.3
unnamed: R804.2, U801.1
unnamed: R804A1.2, U801.4, U801.20
unnamed: R902.2, U303.6
unnamed: R904.2, U800.47
unnamed: R905.2, U800.22
unnamed: RN100.8, U100.12, U303.11
unnamed: RN102.1, U107.8
unnamed: RN102.3, U107.6
unnamed: RN102.5, RN102.7, U107.4
unnamed: RN203E1.2, U205.14
unnamed: RN204A1.1, U202.4
unnamed: RN204B1.1, U202.7
unnamed: RN204C1.1, U202.9
unnamed: RN204D1.1, U202.12
unnamed: RN802.6, RN802.7, U805.11
unnamed: RN802.8, RN802.10, U805.8, U805.13
unnamed: RN902.3, U107.12
unnamed: RN902.5, U107.10
unnamed: RN902.7, U107.2
unnamed: RN903.2, U605.2
unnamed: RN903.3, U605.18
unnamed: RN904.2, U201.23, U205.17
unnamed: RN904.3, U201.22, U205.15
unnamed: RN904.4, U201.21, U205.13
unnamed: RN904.5, U201.20, U205.11
unnamed: RN905.2, U201.27, U206.17
unnamed: RN905.3, U201.26, U206.15
unnamed: RN905.4, U201.25, U206.13
unnamed: RN905.5, U201.24, U206.11
unnamed: RN906.2, U201.31, U206.2
unnamed: RN906.3, U201.30, U206.4
unnamed: RN906.4, U201.29, U206.6
unnamed: RN906.5, U201.28, U206.8
unnamed: RN907A1.2, RN907C1.2, U101.38, U302.9
unnamed: RN907B1.2, U302.8
unnamed: U101.19, U102.19
unnamed: U101.20, U900.12
unnamed: U101.23, U102.18
unnamed: U101.25, U102.20
unnamed: U102.15, U900.8
unnamed: U102.44, U203.13
unnamed: U102.45, U203.10
unnamed: U102.47, U203.2
unnamed: U108.11, U203.5, U900.6
unnamed: U201.18, U205.4
unnamed: U201.33, U205.6
unnamed: U300.23, U302.3
unnamed: U301.23, U302.6
unnamed: U802.9, U803.1
unnamed: U802.10, U804.12
unnamed: U802.11, U804.13
unnamed: U802.12, U803.4
unnamed: U802.13, U803.9
unnamed: U802.14, U804.3
unnamed: U802.15, U803.12
unnamed: U803.3, U804.11
unnamed: U803.6, U804.1
unnamed: U803.8, U804.2
unnamed: U803.11, U804.4
unnamed: U900.10, U900.11
unnamed: U9001.2, U9002.11
unnamed: U9001.4, U9001.5
unnamed: U9001.6, U9002.10
unnamed: U9002.8, U9002.12
unnamed: XC1.1, XR1.2
OVL: U102.30, U300.2
PBUSY: CN203.18, EMI336.1, RN300.6, U301.2, U301.39
PPD0: CN203.23, EMI302.1, U300.10
PPD1: CN203.24, EMI303.1, U300.11
PPD2: CN203.25, EMI304.1, U300.12
PPD3: CN203.26, EMI305.1, U300.13
PPD4: CN203.27, EMI306.1, U300.14
PPD5: CN203.28, EMI307.1, U300.15
PPD6: CN203.29, EMI308.1, U300.16
PPD7: CN203.30, EMI309.1, U300.17
PPOUT: CN203.16, EMI337.1, RN300.7, U301.3, U301.40
PSEL: CN203.21, EMI338.1, Q300.3, RN300.8, U301.4
PSTROBE: CN201.36, EMI301.1, RN300.2, U300.18
R0: CN203.2, R4V1.2, U205.9, VIDIOT1.6
R1: CN203.3, R2V1.2, U205.7, VIDIOT1.5
R2: CN203.4, R3V1.2, U205.5, VIDIOT1.4
R3: R1V1.2, RN201D1.1, U205.3, VIDIOT1.3
RAWLEFT: C240.1, CN203.33, Q200.2, R240.1, R241.2, U204.14
RAWRIGHT: C230.1, CN203.35, Q201.2, R230.1, R231.2, U204.8
READ: C658.2, CN601.68, CN602.68, CN603.68, CN604.68, CN605.68, RN908.2, U605.14, U800.35
RGA1: U101.33, U200.26, U201.17
RGA2: U101.32, U200.25, U201.16
RGA3: U101.31, U200.24, U201.15
RGA4: U101.30, U200.23, U201.14
RGA5: U101.29, U200.22, U201.13
RGA6: U101.28, U200.21, U201.12
RGA7: U101.27, U200.20, U201.11
RGA8: U101.26, U200.19, U201.10
R_W: CN600.68, RN101.6, U100.9, U101.22, U102.12, U300.22, U301.22, U605.6
TBASE: C915.1, CN201.26, CN203.14, R203A1.2, U101.79, U300.19
V7M: CN600.7, RN907C1.1
VCDAC: CN203.15, CN600.15, RN902.6
Vref: C219.1, C224.1, R209.2, R210.1, U204.10, U204.12
XCLK: R110.2, R212.1, U101.35
XRDY: CN600.18, CN601.18, CN602.18, CN603.18, CN604.18, CN605.18, R114.1, U102.31
_AS: CN600.74, RN101.5, U100.6, U101.24, U102.13, U605.9
_BAS: C663.2, CN601.74, CN602.74, CN603.74, CN604.74, CN605.74, RN908.5, U605.11, U800.36
_BEER: CN600.46, CN601.46, CN602.46, CN603.46, CN604.46, CN605.46, R111.2, U100.22, U800.26
_BG: U100.11, U800.17
_BGACK: CN600.62, CN601.62, CN602.62, CN603.62, CN604.62, CN605.62, J900.1, RN100.9, U303.13
_BHS: U205.18, U301.19
_BLDS: C660.2, CN601.70, CN602.70, CN603.70, CN604.70, CN605.70, RN908.3, U605.13, U800.37
_BOSS: CN600.20, R104.2, U303.12, U800.39
_BR: RN100.10, U100.13, U800.27
_BRST: C909.1, R602.2, U108.10, U300.34, U301.34, U607.3, U607.5, U607.10, U607.12, U800.42
_BUDS: C662.2, CN601.72, CN602.72, CN603.72, CN604.72, CN605.72, RN908.4, U605.12, U800.38
_BURST: CN601.94, CN602.94, CN603.94, CN604.94, CN605.94, R603.2
_C2: C904.1, U800.21
_C4: C913.1, C920.1, CN201.19, R905.1
_CASL: U101.54, U541.4
_CASU: U101.55, U541.6
_CBG: CN600.64, R806.1, U800.29
_CBR: CN600.60, R807.1, U800.28
_CDAC: U101.37, U102.26, U107.1, U107.11, U201.34, U800.18
_CIPL0: RN801.6, U200.13, U802.1
_CIPL1: RN801.7, U200.14, U802.2
_CIPL2: RN801.8, U200.15, U802.3
_CLKRD: U102.22, U801.11
_CLKWR: U102.23, U801.13
_COPCFG: CN605.12, RN607.6, U606.12
_CSYNC: C914.2, CN201.14, U101.80, U201.32, U205.8, U205.12, VIDIOT1.18
_CUTOFF: R214.1, U304.3
_D2P: RNX1.2, RNX2.10, U603.1, U604.1, U800.45
_DBOE: U603.19, U604.19, U800.46
_DKRD: CN303.30, R301.2, U200.37
_DKWD: U102.9, U200.38
_DTACK: CN600.66, CN601.66, CN602.66, CN603.66, CN604.66, CN605.66, R106.1, R917.2, RN101.4, U100.10
_EBG1: CN605.64, U800.2
_EBG2: CN604.64, U800.3
_EBG3: CN603.64, U800.4
_EBG4: CN602.64, U800.5
_EBG5: CN601.64, U800.6
_EBR1: CN605.60, RN600.2, U800.7
_EBR2: CN604.60, RN600.3, U800.8
_EBR3: CN603.60, RN600.4, U800.9
_EBR4: CN602.60, RN600.5, U800.10
_EBR5: CN601.60, RN600.6, U800.11
_EC1: CN601.16, CN602.16, CN603.16, CN604.16, CN605.16, RN902.4
_EC3: CN601.14, CN602.14, CN603.14, CN604.14, CN605.14, FB907.1
_EINT1: C675.2, CN601.96, CN602.96, CN603.96, CN604.96, CN605.96, RN801.2, U803.2
_EINT4: CN601.44, CN602.44, CN603.44, CN604.44, CN605.44, RN801.3, U803.5
_EINT5: CN601.42, CN602.42, CN603.42, CN604.42, CN605.42, RN801.4, U803.10
_EINT7: CN601.40, CN602.40, CN603.40, CN604.40, CN605.40, RN801.5, U803.13
_EXRAM: J500.2, R500.2, U102.32
_FIR0: EMI241.2, U300.8
_FIR1: CN203.19, EMI238.2, U101.78, U300.9
_GBG: CN601.95, CN602.95, CN603.95, CN604.95, CN605.95, U800.23
_HLT: CN600.55, CN601.55, CN602.55, CN603.55, CN604.55, CN605.55, RN101.3, U100.17, U102.42
_HSYNC: CN201.22, R203.1, R203B1.2, U101.81, U205.2
_INDEX: CN303.8, RN301.6, U301.24
_INT2: CN600.19, CN601.19, CN602.19, CN603.19, CN604.19, CN605.19, R312.2, U200.16, U300.21
_INT3: U101.17, U200.17
_INT6: CN600.22, CN601.22, CN602.22, CN603.22, CN604.22, CN605.22, R311.2, U200.18, U301.21
_IPL0: CN600.40, RN100.5, U100.25, U804.9
_IPL1: CN600.42, RN100.6, U100.24, U804.7
_IPL2: CN600.44, RN100.7, U100.23, U804.6
_KBCLK: FB302.2, RN300.9, U300.40, U805.6
_KBRST: ATX-RESET1.1, R201.2, U102.5, U805.14
_LATCH: FB102.1, U104.11, U106.11
_LDS: CN600.70, RN101.7, U100.8, U101.52, U102.10, U605.7
_LED: CN203.31, U300.3, U303.5, U304.2
_MC1: R900.2, RN102.8, U202.1
_MTR: U102.7, U108.12, U301.17
_OEB: U102.4, U103.19, U105.19
_OEL: U102.3, U104.1, U106.1
_OVR: CN601.17, CN602.17, CN603.17, CN604.17, CN605.17, R115.1, U102.29, U800.40
_OWN: CN601.7, CN602.7, CN603.7, CN604.7, CN605.7, R800.2, U302.12, U800.41
_PACK: CN203.20, EMI335.1, RN300.5, U300.24
_RAS0: U101.57, U541.8
_RAS1: U101.56, U541.13
_ROMEN: U102.21, U500.12, U900.9
_RST: CN600.53, CN601.53, CN602.53, CN603.53, CN604.53, CN605.53, RN101.2, U100.18, U101.16, U102.41, U200.11, U607.2
_RxD: U200.41, U305.3
_SEL0: CN303.10, U102.16, U301.13
_SEL1: CN303.12, U301.14, U900.5
_SIDE: CN303.32, U301.12
_SLAVE1: CN605.9, RN800.6, U800.12
_SLAVE2: CN604.9, RN800.5, U800.13
_SLAVE3: CN603.9, RN800.4, U800.14
_SLAVE4: CN602.9, RN800.3, U800.15
_SLAVE5: CN601.9, RN800.2, U800.16
_STEP: CN303.20, U301.10
_TxD: U200.40, U304.9, U304.10
_UDS: CN600.72, RN101.8, U100.7, U101.53, U102.11, U605.8
_VC1: CN201.34, CN600.16, RN102.6
_VC3: CN203.17, CN600.14, RN102.4
_VMA: CN600.51, CN601.51, CN602.51, CN603.51, CN604.51, CN605.51, RN101.9, U100.19, U302.2, U302.4
_VPA: CN600.48, CN601.48, CN602.48, CN603.48, CN604.48, CN605.48, R105.1, R1000.2, RN101.10, U100.21
_WE: U101.21, U541.17
_XCLKEN: CN201.16, R109.1, U101.36

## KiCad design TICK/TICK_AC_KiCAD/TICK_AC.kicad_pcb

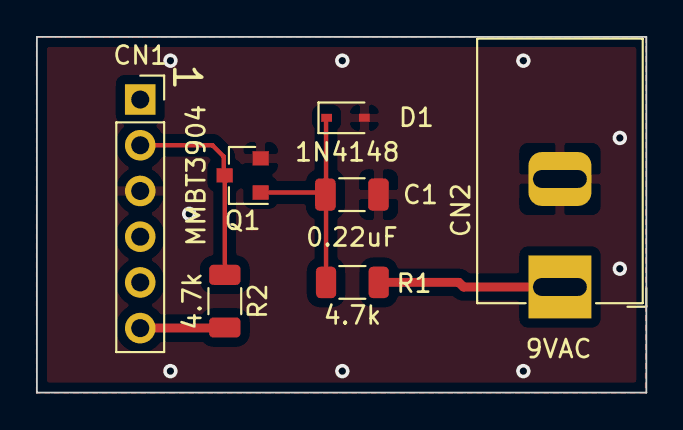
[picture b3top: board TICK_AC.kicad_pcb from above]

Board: 2 copper layers, 33.9 x 19.8 mm, 7 parts (0 on the bottom side), 5 nets.

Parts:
C1: 0.22uF; C_1206_3216Metric
CN1: To_Amiga; PinSocket_1x06_P2.54mm_Vertical
CN2: Barrel_Jack; BarrelJack_Horizontal
D1: 1N4148; D_SOD-323
Q1: MMBT3904; SOT-23
R1, R2: 4.7k; R_1206_3216Metric

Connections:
+5V: CN1.6, R2.2
/+9VAC: CN2.1, R1.2
/TBASE: CN1.2, Q1.3, R2.1
GND: C1.2, CN1.3, CN2.2, D1.2, Q1.2
unnamed: C1.1, D1.1, Q1.1, R1.1

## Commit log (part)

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2021-06-18 Delete 2000EATX-KiCAD-R1 directory
    Delete old revision
2021-07-11 Update README.md
    Updated project status.
2021-07-12 Update Project Status
2021-07-15 Update with current testing status
2021-07-16 Added Agnus 8375
2021-07-22 Update project status.
2021-07-22 Delete 2000EATX-KiCAD-R11 directory
    Delete Deprecated Revision.
2021-07-31 Add jumper locations to User Guide
2021-08-03 Added COP and Video PIC clearance info
2021-08-11 Upload Rev 1.2.1 Final
2021-08-11 Upload Rev PCB 1.2.1 Image
2021-08-12 Gerber for Rev 1.2.1
2021-08-12 Updated to include production board information.
2021-08-12 Update with ordering information
2021-08-14 Added photo of Amiga 2000 EATX in computer case
2021-08-14 Added link to the Gallery page
2021-08-17 Updated SRAM part number
2021-08-21 Add Insane Jumper Edition
    This was a trial run to make schematics to support either 8375 or 8372A with one board. Total jumpers to configure: 34.
2021-09-30 Additional footprints and symbols
2021-11-18 Revision 2.1 BOM and Shopping List
2021-11-18 Amiga 2000 EATX Schematics
2021-12-11 Update README.md
    Updated memory explanation.
2021-12-11 Update AssemblyNotes.md
    Fixed BOM links.
2021-12-21 Update RTC info.
2021-12-21 Added additional details to case selection.
2021-12-21 Updated case selection section.
2021-12-21 Added information to the case selection section.
2021-12-21 Updated case considerations section.
2021-12-23 Corrected part number line 111.
2022-01-04 Update AssemblyNotes.md
    Agnus part numbers 390544-01 and 390544-02 were in the wrong column in Table A3. Fixed.
2022-01-04 Update README.md
    Added issue description for Agnus configuration jumper JA5.
2022-01-05 Updated Rev 2.1 Gerber
    Updated the Agnus configuration table.
2022-01-05 Update Rev 2.1 KiCad Agnus Configuration Jumpers
    Update the agnus configuration jumper tables in the schematics and on the board.
2022-01-05 Delete 2000ATX-Rev21.zip
    Old file.
2022-02-04 Add TICK Board Gerbers
2022-02-04 Add Rev 2.2 KiCAD Files
2022-02-04 Updated for Rev 2.2
2022-02-04 Deprecated
2022-02-04 New with Rev 2.2
2022-02-04 Updated oscillator section.
2022-02-04 Updated Oscillator Section
2022-03-25 Gerber Files
2022-07-17 Updated Digikey Part Numbers
2022-08-10 Add .gitattributes
2022-10-11 Update to include 74F245 change.
2022-10-11 Change U103/105 to 74F245.
2023-01-23 Interactive BOM
2023-02-13 Update Table A2.
2023-02-13 Description of Rev 6.2/A2630/A2091 DMA Issue
2023-03-01 Add dual oscillator TICK.
2023-05-11 Rev 3.0 Schematics
2023-05-11 Rev 3.0 Gerber
2023-05-11 Rev 3.0 IBOM
2023-05-11 Rev 3.0 KiCAD
2024-06-02 Update to Rev 3.1 02-JUN-2024
2024-06-02 Update Schematic 02-JUN-2024
